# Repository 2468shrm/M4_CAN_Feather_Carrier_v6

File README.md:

# M4_CAN_Feather_Carrier_v6

## Board Intent
The carrier board is a platform to utilize the [Adafruit M4 Feather CAN
Express](https://www.adafruit.com/product/4759) in FRC robotic applications.
It was developed primarily for students of FRC teams 2468 ("Team Appreciate"),
2687 ("Team Apprentice"), and 2689 ("Team Alpha"). Alone, the M4 Feather CAN
Express board doesn't easily interface to an FRC robot. However, when connected
to a carrier board the feather board has great application potential due to the
integrated CAN port, the M4-processor's native single-precision floating-point
support, etc. FRC robots use CAN as a communication network for its control
system.

The promise of the platform isn't that one can hook a single sensor to the platform
and send the sendor value over CAN. There are many examples of awesome dedicated circuits
that perform functions like these that would result in a smaller solution
(e.g. [Grapple Robotics LaserCAN](https://www.thethriftybot.com/products/pre-order-grapple-robotics-lasercan)
is a CAN-connected Time-of-Flight sensor). Rather, the platform enables creative
combination of sensors and application-specific processing in an off-roboRIO
accelerator. Moreover, the platform provides a great opportunity to start an embedded
journey.

The platform leverages the use of CircuitPython and easy connect to breakout circuits
from [SparkFun](https://sparkfun.com) and [Adafruit](https://adafruit.com). As
experience is gained with the platform prototype sensor solutions can be developed very rapidly. The platform also provides RIO-like interfacing.

## Board Block Diagram and Features

The following a a simplified block diagram of the carrier board. 

The carrier board provies the following features to simplify integration onto an FRC robot:

- Socket for M4 Feather CAN Express board (4).
  - M4 Feather CAN Express board suitable for [CircuitPython](https://circuitpython.org/) use.
  - Jumper (U) allows carrier board 5V supply to feed back on USB-C VBUS.
  - For connecting to and powering USB-C devices when M4 board is acting as USB host.
  - Uses Wago 2601-3102 latching terminal block for wire attachment. 16-24 AWG.

- Socket for [Adafruit Ethernet FeatherWing](https://www.adafruit.com/product/3201) (N).
  - Provides ability to use an alternate networking interface; when CAN isn't appropriate.
  - Socket inapproriate for other FeatherWing due to SPI chip select use.

- Battery-friendly power input (P).
  - Wago 2601-3102 wire to board connection (D).
  - Convert 12V to 5V.
  - Output 5V @ 2.5A.
  - 12V and 5V indicator LEDs, D102 and D102, respectively.

- 4 digital input/outputs (DIOs) (IO and L).
  - A 4x3 header pin block (J3) provides roboRIO similar digital interface.
  - Signal, Power, and Ground for each digital I/O.
  - Jumper (J5) provides selectable power to DIO header ppwer pins.
  - I/Os use level shifter.
  - Each I/O has an LED indicating logical value (high = LED on, low = LED off).

- 4 analog inputs (AI).
  - Input range is 0V-3.3V.
  - Buffered through rail-to-rail operational amplifier in unity gain configuration.
  - A 4x3 header pin block () provides roboRIO similar analog interface.

- 3 Qwiic / STEMMA QT compatible interfaces (X1, X2, and X4).
  - X1 is 3.3V only.
  - X2 and X4 use a slide switch to provide either 3.3V or 5V on the connector power pins and also includes a level shifter.
  - X2 and X4 are intended to connect to the TFMini-S or LiDAR Lite.

- MicroSD card socket (M)
  - Uses SPI mode/interfacing.

- A Neopixel interface (E).
  - Intended use is to provide visual communication of processed results.
  - Uses Wago 2601-3103 latching terminal block for wire attachment. 16-24 AWG.

The interfaces described above are shown in the following annotated board render.

The following diagram provides more detail to the pins for some of the board's connectors.

The 4x3 and 4x2 pin headers are shown to indicate their function. Ground pins have a
green box, power pins have a red box, and signal pins have a white box. These header
follows the RIO organization (modeled on the servo interface).

For the Analog In signals, the power is 3.3V (sourced from the M4 Feather CAN Express
board).

For the DIOs, the power is controlled by a 2 position jumper (J5) adjacent to the DIO header.
The diagram shows the jumper position for the applied voltage.
- 3.3V is selected by jumpering the middle pin to the inner pin.
- 5V is selected by jumpering the middle pin to the outer pin.

The DIO signals connect to the M4 microcontroller through a level shifter. The level
shifter VCCB supply is powered from the same voltage as the middle pin.

The DIOs are also accompanied by a 4x2 pin header that provides the same power and ground
as the 4x3. The intent for this arrangement is to be able to connect 4 [beam break
emitter/detactor pairs](https://www.adafruit.com/product/2168) to the DIOs. 

Connectors X2 and X4 are modified Qwiic connectors. The switches adjacent to X2 and X4
allow the power provided to their respective connector to be either 3.3V or 5V.
- 3.3V is selected by sliding the switch to the left.
- 5V is selected by sliding the switch to the right.

Both of these Qwiic / STEMMA QT connections include a level shifter between connector
and the M4 microcontroller. This flexibility on X2 and X4 is intended to allow the
connection of 5V I2C sensors such as the Garmin LiDAR Lite (v3 and v4) and the
TFMini-S sensor. 

Connector X1 is a regular Qwiic connector that uses 3.3V for supplying power to the
breakout board.

The Neopixel is a 3 pin interface. To facilitate a connection to an LED string with
soldered on wires, a Wago 2601-3103 connector is provided for wire to board. This
allows the use of stripped wire (or with crimped ferrules) instead of needing a PWM
style connector.

The battery connection is made through a Wago 2601-3102.

The sockets for the Feather and FeatherWing boards are shown in the following diagram.
These are not interchangable. Nor is the FeatherWing socket capable of working with
a FeatherWing other than the Ethernet FeatherWing.

The power circuit for the carrier board is shown in the following diagram.

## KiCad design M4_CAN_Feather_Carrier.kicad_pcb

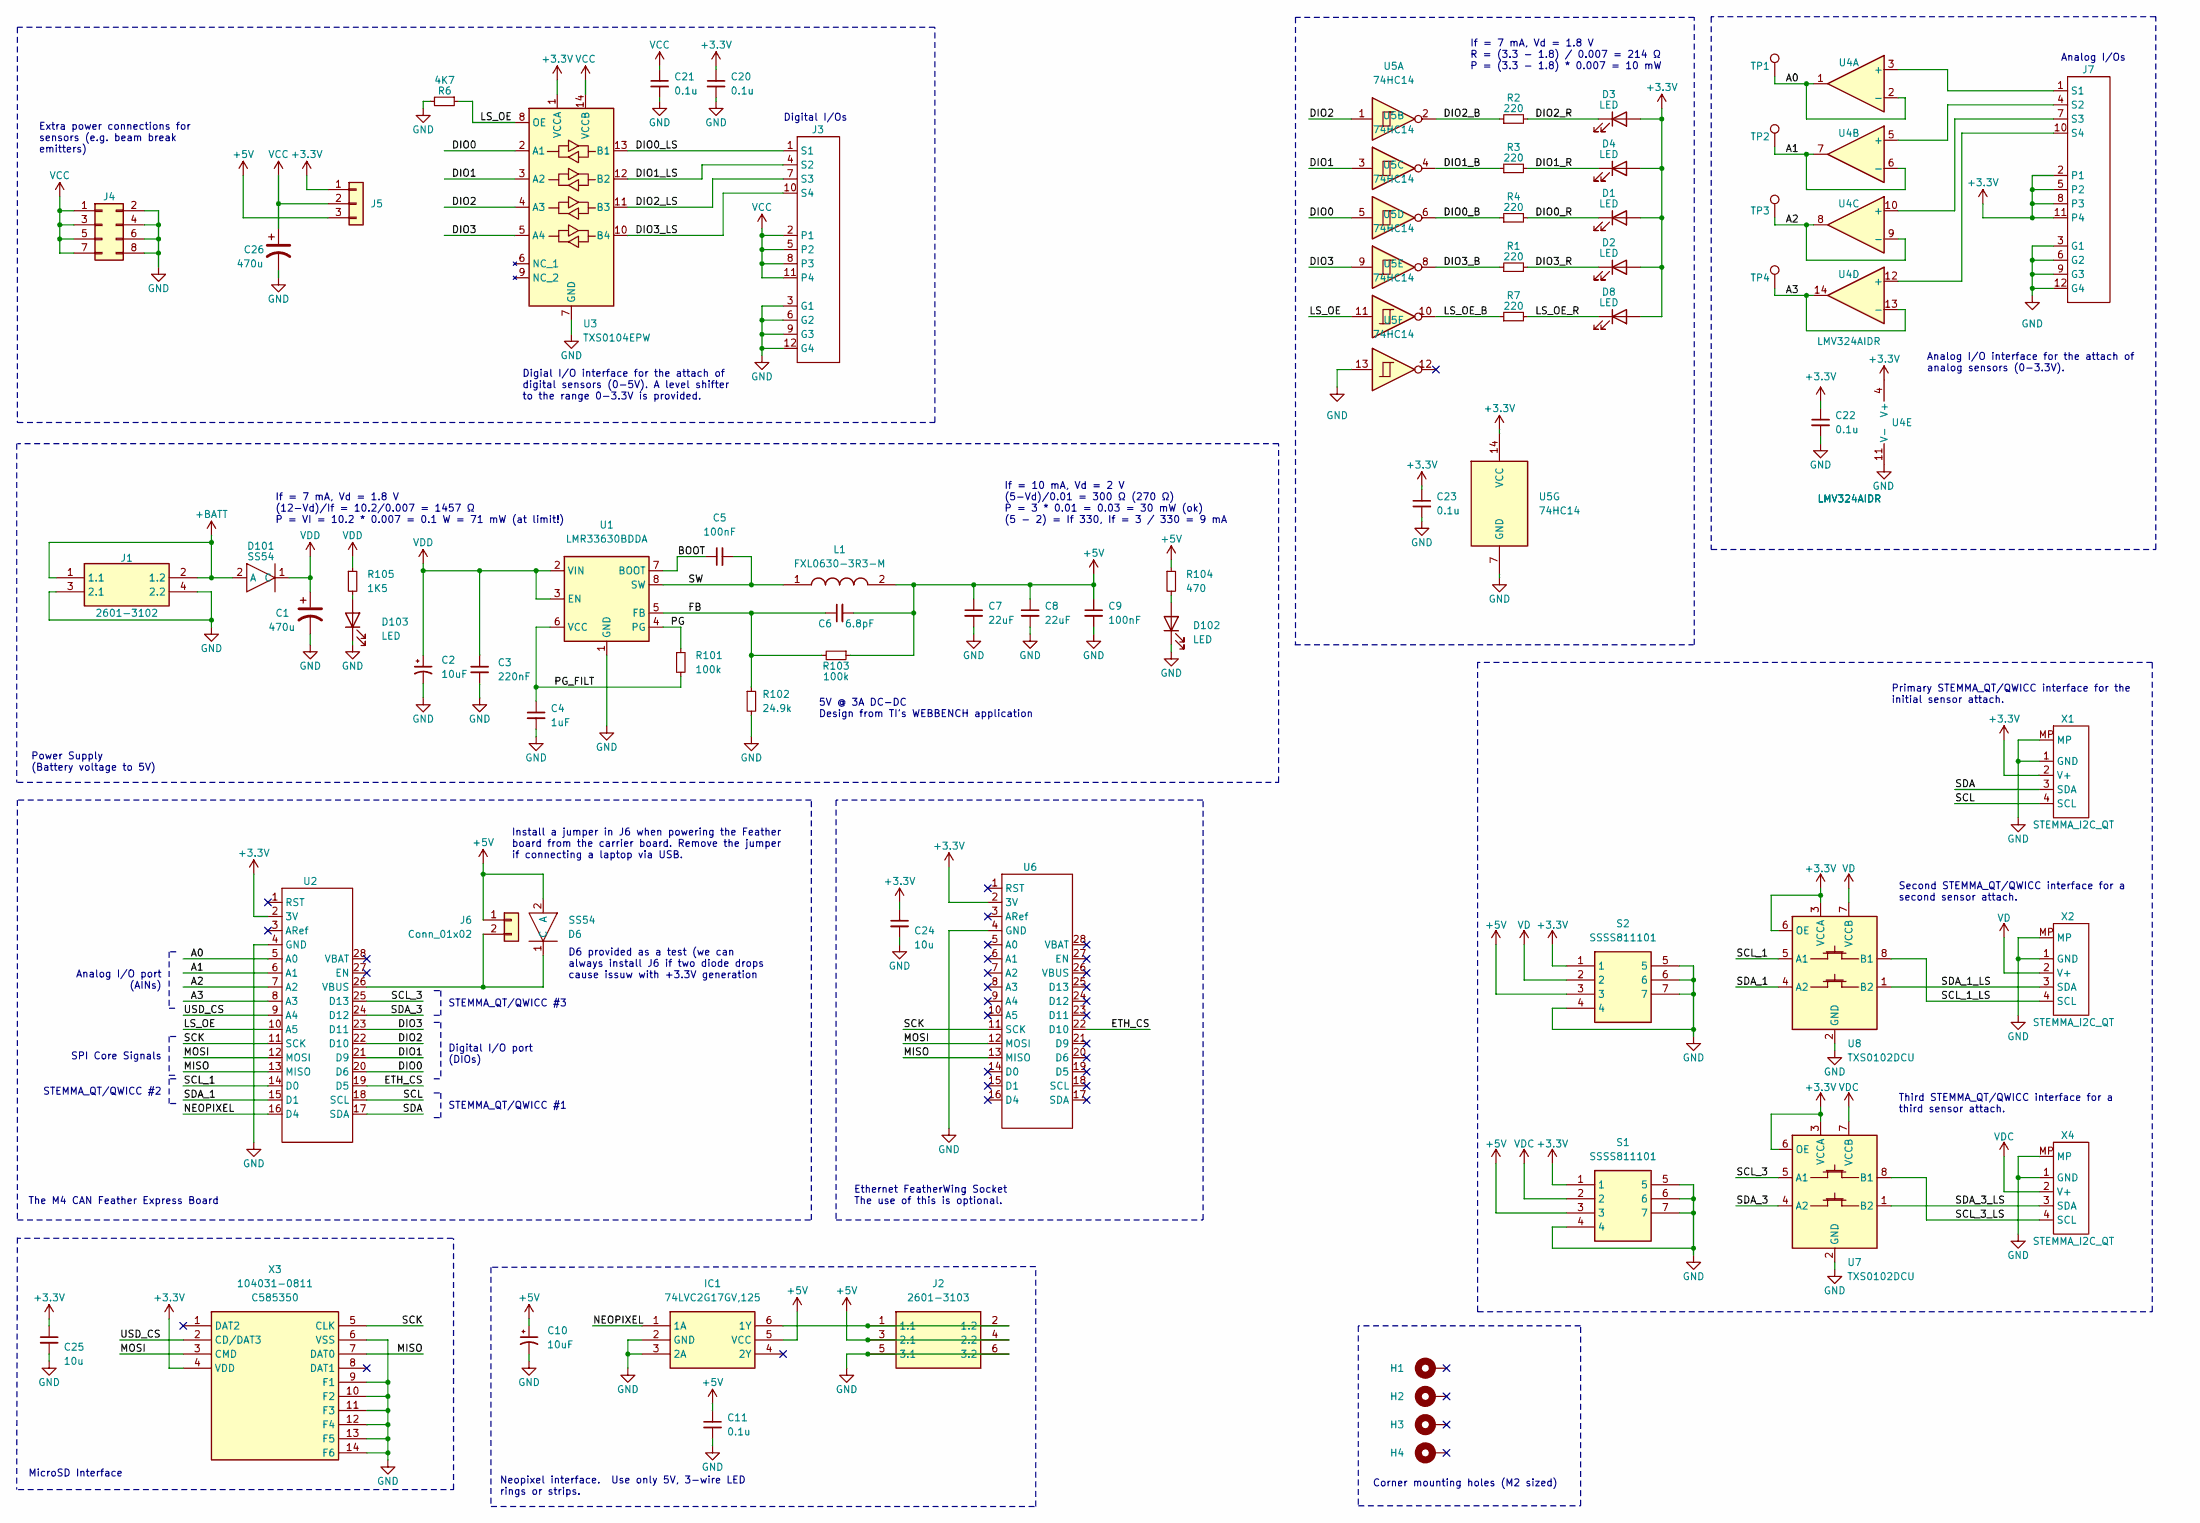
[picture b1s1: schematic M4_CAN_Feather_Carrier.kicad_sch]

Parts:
C1, C26: 470u; CP_Elec_8x10; LCSC C2164760
C2, C10: 10uF; C_0603_1608Metric; LCSC C96446
C3: 220nF; C_0603_1608Metric; LCSC C21120
C4: 1uF; C_0603_1608Metric; LCSC C59302
C5, C9: 100nF; C_0603_1608Metric; LCSC C14663
C6: 6.8pF; C_0603_1608Metric; LCSC C1679
C7, C8: 22uF; C_0805_2012Metric; LCSC C45783
C11, C20, C21, C22, C23: 0.1u; C_0603_1608Metric; LCSC C14663
C24, C25: 10u; C_0603_1608Metric; LCSC C96446
D1, D2, D3, D4, D8, D102, D103: LED; LED_0603_1608Metric; LCSC C2286
D6, D101: SS54; DO-214AC; LCSC C22452
H1, H2, H3, H4: MountingHole_Pad; MountingHole_2.2mm_M2_DIN965_Pad
IC1: 74LVC2G17GV,125; SOT95P275X110-6N; Manufacturer_Part_Number 74LVC2G17GV,125; Mouser Part Number 771-74LVC2G17GV-G
J1: 2601-3102; 26013102; Manufacturer_Part_Number 2601-3102
J2: 2601-3103; 26013103; Manufacturer_Part_Number 2601-3103
J3, J7: conn_04_03; conn_04x03
J4: Conn_02x04_Odd_Even; PinHeader_2x04_P2.54mm_Vertical
J5: Conn_01x03; PinHeader_1x03_P2.54mm_Vertical
J6: Conn_01x02; PinHeader_1x02_P2.54mm_Vertical
L1: FXL0630-3R3-M; FXL0630; Manufacturer_Part_Number ASPI-0804T-150M-T; LCSC C167219
R1, R2, R3, R4, R7: 220; R_0603_1608Metric; LCSC C22962
R6: 4K7; R_0603_1608Metric; LCSC C23162
R101, R103: 100k; R_0603_1608Metric; LCSC C25803
R102: 24.9k; R_0603_1608Metric; LCSC C25962
R104: 470; R_0603_1608Metric; LCSC C23179
R105: 1K5; R_0603_1608Metric; LCSC C22843
S1, S2: SSSS811101; Manufacturer_Part_Number SSSS811101; Mouser Part Number 688-SSSS811101
TP1, TP2, TP3, TP4: TestPoint; TestPoint_Pad_1.5x1.5mm
U1: LMR33630BDDA; Texas_HSOP-8-1EP_3.9x4.9mm_P1.27mm_ThermalVias; LCSC C544370
U2, U6: Feather_M4_CAN_Express
U3: TXS0104EPW; TSSOP-14_4.4x5mm_P0.65mm; LCSC C44955
U4: LMV324AIDR; SOIC-14_3.9x8.7mm_P1.27mm; LCSC C484732
U5: 74HC14; TSSOP-14_4.4x5mm_P0.65mm; LCSC C2866133
U7, U8: TXS0102DCU; VSSOP-8_2.3x2mm_P0.5mm; LCSC C53434
X1, X2, X4: STEMMA_I2C_QT; JST_SH_BM04B-SRSS-TB_1x04-1MP_P1.00mm_Vertical; LCSC C160390
X3: 104031-0811; 1040310811; Manufacturer_Part_Number 104031-0811; Mouser Part Number 538-104031-0811

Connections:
+3.3V: C20.1, C22.1, C23.1, C24.1, C25.1, D1.2 (A), D2.2 (A), D3.2 (A), D4.2 (A), D8.2 (A), J5.1, J7.2 (P1), J7.5 (P2), J7.8 (P3), J7.11 (P4), S1.1, S2.1, U2.2 (3V), U3.1 (VCCA), U4.4 (V+), U5.14 (VCC), U6.2 (3V), U7.3 (VCCA), U7.6 (OE), U8.3 (VCCA), U8.6 (OE), X1.2 (V+), X3.4 (VDD)
+5V: C6.2, C7.1, C8.1, C9.1, C10.1, C11.1, D6.2 (A), IC1.5 (VCC), J2.3 (2.1), J2.4 (2.2), J5.3, J6.1, L1.2, R103.1, R104.1, S1.3, S2.3
+BATT: D101.2 (A), J1.1 (1.1), J1.2 (1.2)
/A0: TP1.1, U2.5 (A0), U4.1, U4.2 (-)
/A1: TP2.1, U2.6 (A1), U4.6 (-), U4.7
/A2: TP3.1, U2.7 (A2), U4.8, U4.9 (-)
/A3: TP4.1, U2.8 (A3), U4.13 (-), U4.14
/BOOT: C5.1, U1.7 (BOOT)
/DIO0: U2.20 (D6), U3.2 (A1), U5.5
/DIO0_B: R4.1, U5.6
/DIO0_LS: J3.1 (S1), U3.13 (B1)
/DIO0_R: D1.1 (K), R4.2
/DIO1: U2.21 (D9), U3.3 (A2), U5.3
/DIO1_B: R3.1, U5.4
/DIO1_LS: J3.4 (S2), U3.12 (B2)
/DIO1_R: D4.1 (K), R3.2
/DIO2: U2.22 (D10), U3.4 (A3), U5.1
/DIO2_B: R2.1, U5.2
/DIO2_LS: J3.7 (S3), U3.11 (B3)
/DIO2_R: D3.1 (K), R2.2
/DIO3: U2.23 (D11), U3.5 (A4), U5.9
/DIO3_B: R1.1, U5.8
/DIO3_LS: J3.10 (S4), U3.10 (B4)
/DIO3_R: D2.1 (K), R1.2
/ETH_CS: U2.19 (D5), U6.22 (D10)
/FB: C6.1, R102.1, R103.2, U1.5 (FB)
/LS_OE: R6.1, U2.10 (A5), U3.8 (OE), U5.11
/LS_OE_B: R7.1, U5.10
/LS_OE_R: D8.1 (K), R7.2
/MISO: U2.13 (MISO), U6.13 (MISO), X3.7 (DAT0)
/MOSI: U2.12 (MOSI), U6.12 (MOSI), X3.3 (CMD)
/NEOPIXEL: IC1.1 (1A), U2.16 (D4)
/PG: R101.1, U1.4 (PG)
/PG_FILT: C4.1, R101.2, U1.6 (VCC)
/SCK: U2.11 (SCK), U6.11 (SCK), X3.5 (CLK)
/SCL: U2.18 (SCL), X1.4 (SCL)
/SCL_1: U2.14 (D0), U8.5 (A1)
/SCL_1_LS: U8.8 (B1), X2.4 (SCL)
/SCL_3: U2.25 (D13), U7.5 (A1)
/SCL_3_LS: U7.8 (B1), X4.4 (SCL)
/SDA: U2.17 (SDA), X1.3 (SDA)
/SDA_1: U2.15 (D1), U8.4 (A2)
/SDA_1_LS: U8.1 (B2), X2.3 (SDA)
/SDA_3: U2.24 (D12), U7.4 (A2)
/SDA_3_LS: U7.1 (B2), X4.3 (SDA)
/SW: C5.2, L1.1, U1.8 (SW)
/USD_CS: U2.9 (A4), X3.2 (CD/DAT3)
GND: C1.2, C2.2, C3.2, C4.2, C7.2, C8.2, C9.2, C10.2, C11.2, C20.2, C21.2, C22.2, C23.2, C24.2, C25.2, C26.2, D102.1 (K), D103.1 (K), IC1.2 (GND), IC1.3 (2A), J1.3 (2.1), J1.4 (2.2), J2.5 (3.1), J2.6 (3.2), J3.3 (G1), J3.6 (G2), J3.9 (G3), J3.12 (G4), J4.2, J4.4, J4.6, J4.8, J7.3 (G1), J7.6 (G2), J7.9 (G3), J7.12 (G4), R6.2, R102.2, S1.4, S1.5, S1.6, S1.7, S2.4, S2.5, S2.6, S2.7, U1.1 (GND), U1.9 (GND), U2.4 (GND), U3.7 (GND), U4.11 (V-), U5.7 (GND), U5.13, U6.4 (GND), U7.2 (GND), U8.2 (GND), X1.1 (GND), X1.MP, X2.1 (GND), X2.MP, X3.6 (VSS), X3.9 (F1), X3.10 (F2), X3.11 (F3), X3.12 (F4), X3.13 (F5), X3.14 (F6), X4.1 (GND), X4.MP
unnamed: D6.1 (C), J6.2, U2.26 (VBUS)
unnamed: D102.2 (A), R104.2
unnamed: D103.2 (A), R105.2
unnamed: IC1.6 (1Y), J2.1 (1.1), J2.2 (1.2)
unnamed: J7.1 (S1), U4.3 (+)
unnamed: J7.4 (S2), U4.5 (+)
unnamed: J7.7 (S3), U4.10 (+)
unnamed: J7.10 (S4), U4.12 (+)
VCC: C21.1, C26.1, J3.2 (P1), J3.5 (P2), J3.8 (P3), J3.11 (P4), J4.1, J4.3, J4.5, J4.7, J5.2, U3.14 (VCCB)
VD: S2.2, U8.7 (VCCB), X2.2 (V+)
VDC: S1.2, U7.7 (VCCB), X4.2 (V+)
VDD: C1.1, C2.1, C3.1, D101.1 (C), R105.1, U1.2 (VIN), U1.3 (EN)

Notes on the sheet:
Corner mounting holes (M2 sized)
Digital I/Os
Install a jumper in J6 when powering the Feather board from the carrier board. Remove the jumper if connecting a laptop via USB.
Analog I/Os
5V @ 3A DC-DC Design from TI's WEBBENCH application
Primary STEMMA_QT/QWICC interface for the initial sensor attach.
Extra power connections for sensors (e.g. beam break emitters)
Digial I/O interface for the attach of digital sensors (0-5V). A level shifter to the range 0-3.3V is provided.
The M4 CAN Feather Express Board
Second STEMMA_QT/QWICC interface for a second sensor attach.
If = 10 mA, Vd = 2 V (5-Vd)/0.01 = 300 Ω (270 Ω) P = 3 * 0.01 = 0.03 = 30 mW (ok) (5 - 2) = If 330, If = 3 / 330 = 9 mA
Digital I/O port (DIOs)
MicroSD Interface
Analog I/O port (AINs)
STEMMA_QT/QWICC #1
If = 7 mA, Vd = 1.8 V (12-Vd)/If = 10.2/0.007 = 1457 Ω P = VI = 10.2 * 0.007 = 0.1 W = 71 mW (at limit!)
STEMMA_QT/QWICC #2
SPI Core Signals
Analog I/O interface for the attach of analog sensors (0-3.3V).
STEMMA_QT/QWICC #3
Neopixel interface. Use only 5V, 3-wire LED rings or strips.
Power Supply (Battery voltage to 5V)
Ethernet FeatherWing Socket The use of this is optional.
D6 provided as a test (we can always install J6 if two diode drops cause issuw with +3.3V generation
Third STEMMA_QT/QWICC interface for a third sensor attach.
If = 7 mA, Vd = 1.8 V R = (3.3 - 1.8) / 0.007 = 214 Ω P = (3.3 - 1.8) * 0.007 = 10 mW

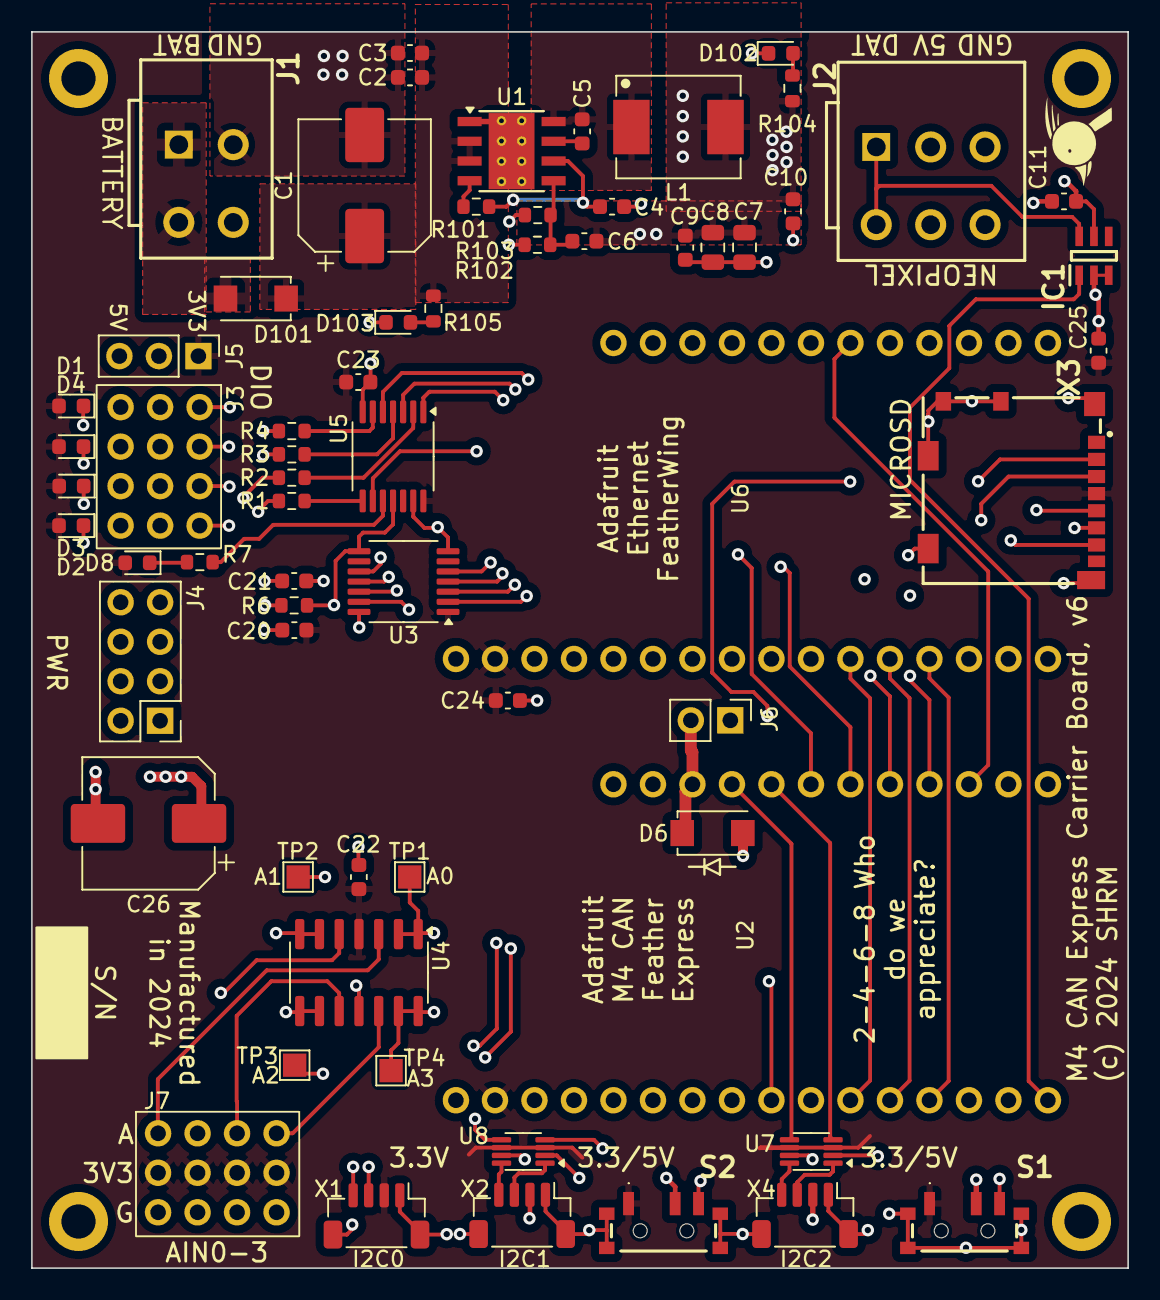
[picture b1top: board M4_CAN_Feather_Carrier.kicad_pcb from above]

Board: 4 copper layers, 70.5 x 79.5 mm, 69 parts (0 on the bottom side), 60 nets.

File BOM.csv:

Comment,Designator,Footprint,LCSC
"470u","C1","Appreciate:CAPAE830X1050N","C340767"
"470u","C26","Appreciate:CAPAE830X1050N","C340767"
"10uF","C2","Capacitor_SMD:C_0603_1608Metric","C96446"
"10uF","C10","Capacitor_SMD:C_0603_1608Metric","C96446"
"0.1u","C20","Capacitor_SMD:C_0603_1608Metric","C14663"
"0.1u","C21","Capacitor_SMD:C_0603_1608Metric","C14663"
"0.1u","C22","Capacitor_SMD:C_0603_1608Metric","C14663"
"0.1u","C23","Capacitor_SMD:C_0603_1608Metric","C14663"
"10u","C24","Capacitor_SMD:C_0603_1608Metric","C96446"
"10u","C25","Capacitor_SMD:C_0603_1608Metric","C96446"
"220nF","C3","Capacitor_SMD:C_0603_1608Metric","C21120"
"1uF","C4","Capacitor_SMD:C_0603_1608Metric","C59302"
"100nF","C5","Capacitor_SMD:C_0603_1608Metric","C14663"
"100nF","C9","Capacitor_SMD:C_0603_1608Metric","C14663"
"6.8pF","C6","Capacitor_SMD:C_0603_1608Metric","C1679"
"22uF","C7","Capacitor_SMD:C_0805_2012Metric","C45783"
"22uF","C8","Capacitor_SMD:C_0805_2012Metric","C45783"
"LED","D1","LED_SMD:LED_0603_1608Metric","C2286"
"LED","D2","LED_SMD:LED_0603_1608Metric","C2286"
"LED","D3","LED_SMD:LED_0603_1608Metric","C2286"
"LED","D4","LED_SMD:LED_0603_1608Metric","C2286"
"LED","D8","LED_SMD:LED_0603_1608Metric","C2286"
"LED","D102","LED_SMD:LED_0603_1608Metric","C2286"
"LED","D103","LED_SMD:LED_0603_1608Metric","C2286"
"SS54","D6","Appreciate:DO-214AC","C22452"
"SS54","D101","Appreciate:DO-214AC","C22452"
"FXL0630-3R3-M","L1","Appreciate:FXL0630","C167219"
"220","R1","Resistor_SMD:R_0603_1608Metric","C22962"
"220","R2","Resistor_SMD:R_0603_1608Metric","C22962"
"220","R3","Resistor_SMD:R_0603_1608Metric","C22962"
"220","R4","Resistor_SMD:R_0603_1608Metric","C22962"
"220","R7","Resistor_SMD:R_0603_1608Metric","C22962"
"100k","R101","Resistor_SMD:R_0603_1608Metric","C25803"
"100k","R103","Resistor_SMD:R_0603_1608Metric","C25803"
"24.9k","R102","Resistor_SMD:R_0603_1608Metric","C25962"
"470","R104","Resistor_SMD:R_0603_1608Metric","C23179"
"1K5","R105","Resistor_SMD:R_0603_1608Metric","C22843"
"4K7","R6","Resistor_SMD:R_0603_1608Metric","C23162"
"SSSS811101","S1","Appreciate:SSSS811101","C109335"
"SSSS811101","S2","Appreciate:SSSS811101","C109335"
"LMR33630BDDA","U1","Package_SO:Texas_HSOP-8-1EP_3.9x4.9mm_P1.27mm_ThermalVias","C544370"
"TXS0104EPW","U3","Package_SO:TSSOP-14_4.4x5mm_P0.65mm","C44955"
"LMV324AIDR","U4","Package_SO:SOIC-14_3.9x8.7mm_P1.27mm","C484732"
"74HC14","U5","Package_SO:TSSOP-14_4.4x5mm_P0.65mm","C2866133"
"TXS0102DCU","U7","Package_SO:VSSOP-8_2.3x2mm_P0.5mm","C53434"
"TXS0102DCU","U8","Package_SO:VSSOP-8_2.3x2mm_P0.5mm","C53434"
"STEMMA_I2C_QT","X1","Connector_JST:JST_SH_BM04B-SRSS-TB_1x04-1MP_P1.00mm_Vertical","C160390"
"STEMMA_I2C_QT","X2","Connector_JST:JST_SH_BM04B-SRSS-TB_1x04-1MP_P1.00mm_Vertical","C160390"
"STEMMA_I2C_QT","X4","Connector_JST:JST_SH_BM04B-SRSS-TB_1x04-1MP_P1.00mm_Vertical","C160390"
"104031-0811","X3","Appreciate:1040310811","C585350"

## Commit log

2024-08-30 Create README.md
    Empty readme.
2024-08-30 A quick update
2024-08-30 Adding some images for use in the README.md
2024-08-30 The source for the images
2024-08-30 Images and diagrams
2024-08-30 KiCAD files
2024-08-30 Updating README, slowly
2024-08-30 Updated README.md to add references to most of the images.
2024-08-30 Build of Materials and component position files for assembly
2024-08-30 Gerbers for PCB manufacture
2024-08-30 Mechanical CAD file of PCB and components
2024-08-31 Updated description for each figure
2025-01-04 KiCAD files (initial)
2025-01-04 Gerber files for builting
2025-01-04 BOM and part position files formatted for JLCPCB
2025-01-04 Some DrawIO and Affinity Designer formatted files for documentation

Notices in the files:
M4_CAN_Feather_Carrier.kicad_pcb:
All Rights Reserved
(c) 2024 SHRM
